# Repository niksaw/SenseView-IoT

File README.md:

# SenseView – Modular IoT Environmental Monitoring Platform

> **An end-to-end IoT platform engineered from concept to deployment, integrating custom hardware, embedded firmware, and a scalable edge-to-cloud data pipeline.**

## Overview

SenseView is a battery-powered IoT environmental monitoring platform developed to demonstrate the complete lifecycle of an embedded IoT system—from hardware design and firmware development to data acquisition, visualization, and cloud integration.

Originally developed as part of a Master's thesis in Electrical and Microsystems Engineering, the project was driven by research objectives emphasizing measurement quality, reliability, modularity, and low-power operation rather than minimizing hardware cost. Consequently, hardware and sensor selection were based on engineering requirements rather than cost optimization.

The platform combines a custom-designed ESP32-C6 sensor node, modular embedded firmware, and a complete MQTT-based backend capable of simultaneously storing data in both local and cloud time-series databases. Although the current implementation uses Zigbee communication, the architecture was intentionally designed to support future migration to Wi-Fi or Thread/Matter with minimal changes.

---

# System Architecture

---

# Engineering Highlights

- Designed and manufactured a custom ESP32-C6 PCB using KiCad.
- Developed embedded firmware for environmental sensing, sensor validation, preprocessing, fault detection, battery monitoring, and automated irrigation control.
- Built a complete MQTT-based IoT backend using Mosquitto, Telegraf, InfluxDB, and Grafana.
- Implemented simultaneous local and cloud data storage using Telegraf dual-output configuration.
- Designed the communication layer to remain extensible to Zigbee, Wi-Fi, and Thread/Matter.
- Designed a custom deployment enclosure using SolidWorks.
- Integrated environmental sensing, data visualization, and irrigation control into a single modular IoT platform.

---

# Technology Stack

| Category | Technology |
|-----------|------------|
| Microcontroller | ESP32-C6 |
| Sensors | SCD40, BME680, TSL2591, SEN0193 |
| Communication | Zigbee (Extensible to Wi-Fi & Thread/Matter) |
| Firmware | Arduino Framework (C++) |
| MQTT Broker | Mosquitto |
| Data Collection | Telegraf |
| Database | InfluxDB + InfluxDB Cloud |
| Dashboard | Grafana + Grafana Cloud |
| PCB Design | KiCad |
| Mechanical Design | SolidWorks |

---

# Gallery

## Complete Device
Battery-powered prototype assembled inside the custom enclosure prior to deployment.

## Custom PCB
PCB integrating the ESP32-C6, environmental sensors, battery management, and expansion headers.

## Grafana Dashboard
Real-time visualization of environmental data collected from the deployed sensor node

## Deployment
Prototype deployed for indoor environmental monitoring

---

# Hardware

## Microcontroller

- ESP32-C6 Development Board

## Sensors

| Sensor | Purpose |
|---------|----------|
| Sensirion SCD40 | CO₂ Concentration |
| Bosch BME680 | Temperature, Humidity, Pressure, VOC |
| Adafruit TSL2591 | Ambient Light |
| DFRobot SEN0193 | Soil Moisture |

## Additional Hardware

- Custom PCB
- Li-Po Battery
- Solenoid Valve
- Custom 3D Printed Enclosure

---

# Software Architecture

## Embedded Firmware

- Sensor acquisition
- Sensor validation
- Data preprocessing
- Battery monitoring
- Irrigation control
- Fault detection

## Communication

- Zigbee
- Zigbee2MQTT

## Backend

- Mosquitto MQTT Broker
- Telegraf
- Local InfluxDB
- InfluxDB Cloud
- Local Grafana
- Grafana Cloud

---

# Repository Structure

```text
firmware/
    ESP32-C6 firmware

hardware/
    bom/
    gerbers/
    kicad/

enclosure/
    SolidWorks enclosure

images/
    architecture/
    dashboard/
    hardware/
    showcase/
```

---
# Engineering Decisions

| Decision | Reason |
|----------|--------|
| ESP32-C6 | Supports Zigbee, Wi-Fi and native Thread, enabling a modular communication architecture. |
| Zigbee | Low-power communication suitable for battery-operated IoT devices and readily available laboratory infrastructure. |
| BME680 | Higher measurement capability including VOC sensing compared to BME280. |
| Custom PCB | Improved robustness, compactness and deployment reliability compared to breadboard prototypes. |
| Telegraf | Flexible preprocessing and simultaneous transmission to both local and cloud InfluxDB instances. |

---

# Engineering Challenges

Some of the most significant engineering challenges encountered during this project included:

- Designing a reliable battery-powered power supply and custom PCB.
- Developing a complete IoT backend from MQTT through cloud visualization.
- Developing custom Zigbee2MQTT integration for seamless communication with the local IoT infrastructure.
- Designing a modular architecture capable of supporting future communication technologies with minimal hardware changes.

---

# Future Improvements

- Wi-Fi communication backend
- Native Thread / Matter implementation
- OTA firmware updates
- Further power optimization
- Configuration interface
- Mobile application

---

# Project Background

This project was developed as part of a Master's thesis in Electrical and Microsystems Engineering at OTH Regensburg.

Rather than focusing on building a single-purpose plant monitoring device, the objective was to engineer a reusable IoT platform capable of supporting environmental sensing applications while remaining modular, scalable and suitable for future communication technologies.

---

# Acknowledgements

I would like to thank my thesis supervisor and OTH Regensburg for providing the opportunity and research environment for this project.

---

# License

This project is licensed under the MIT License.

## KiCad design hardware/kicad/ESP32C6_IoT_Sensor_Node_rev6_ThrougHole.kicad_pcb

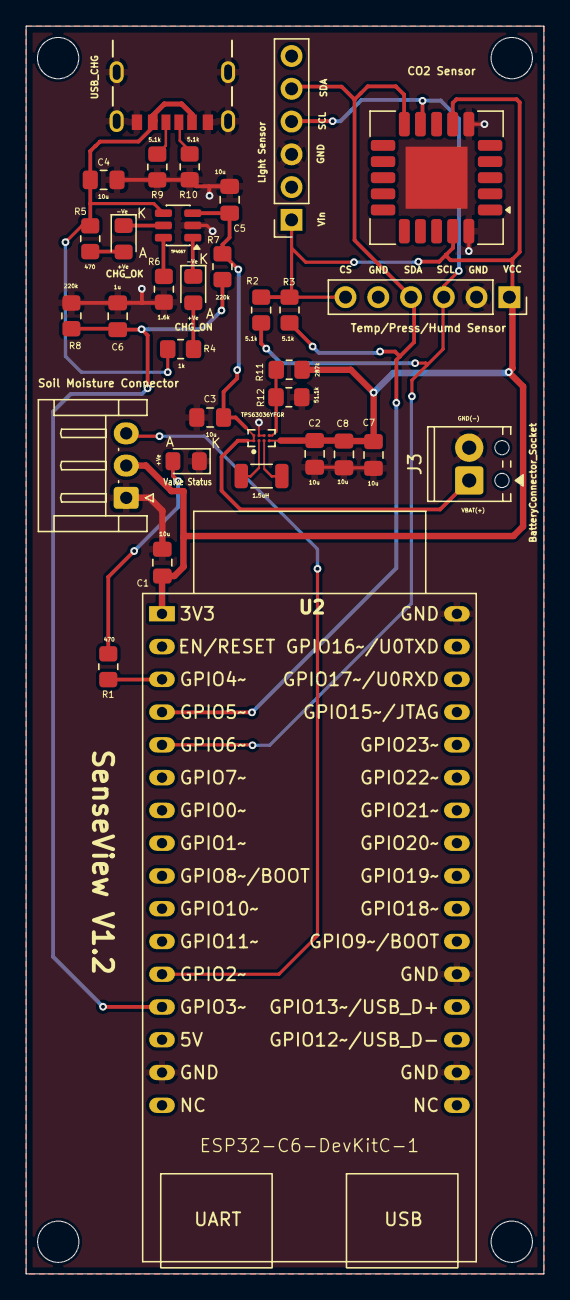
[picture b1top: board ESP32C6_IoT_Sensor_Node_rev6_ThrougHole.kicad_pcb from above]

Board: 2 copper layers, 40.1 x 96.7 mm, 33 parts (0 on the bottom side), 20 nets.

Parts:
C1, C2, C3, C4, C5, C7, C8: 10u; C_0805_2012Metric_Pad1.18x1.45mm_HandSolder
C6: 1u; C_0805_2012Metric_Pad1.18x1.45mm_HandSolder
D1: CHG_OK; LED_0805_2012Metric_Pad1.15x1.40mm_HandSolder
D2: Valve Status; LED_0805_2012Metric_Pad1.15x1.40mm_HandSolder
D3: CHG_ON; LED_0805_2012Metric_Pad1.15x1.40mm_HandSolder
J1: Soil Moisture Connector; JST_EH_S3B-EH_1x03_P2.50mm_Horizontal
J2: USB_CHG; MOLEX_2171750001
J3: BatteryConnector_Socket; TerminalBlock_Phoenix_MPT-0,5-2-2.54_1x02_P2.54mm_Horizontal
L1: 1.5uH; L_1206_3216Metric
R1, R5: 470; R_0805_2012Metric_Pad1.20x1.40mm_HandSolder
R2, R3, R9, R10: 5.1k; R_0805_2012Metric_Pad1.20x1.40mm_HandSolder
R4: 1k; R_0805_2012Metric_Pad1.20x1.40mm_HandSolder
R6: 1.6k; R_0805_2012Metric_Pad1.20x1.40mm_HandSolder
R7, R8: 220k; R_0805_2012Metric_Pad1.20x1.40mm_HandSolder
R11: 287k; R_0805_2012Metric_Pad1.20x1.40mm_HandSolder
R12: 51.1k; R_0805_2012Metric_Pad1.20x1.40mm_HandSolder
U1: Temp/Press/Humd Sensor; PinSocket_1x06_P2.54mm_Vertical
U2: ESP32-C6-DevKitC-1
U3: CO2 Sensor; Sensirion_SCD4x-1EP_10.1x10.1mm_P1.25mm_EP4.8x4.8mm
U4: Light Sensor; PinSocket_1x06_P2.54mm_Vertical
U5: TP4057; TSOT-23-6
U6: TPS63036YFGR; BGA8N40P4X2_181X107X62N

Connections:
5V: C4.1, J2.A9 (VBUS1), J2.B9 (VBUS2), R4.1, R5.1, U5.4 (V_{CC})
+3.3V: C1.1, C2.1, C7.1, C8.1, J1.2, R2.2, R3.2, R11.2, U1.1 (VCC), U1.6 (CS), U2.1 (3V3), U3.7 (VDD), U3.19 (VDD), U4.1 (VIN), U6.D1 (VOUT)
ADC: C6.1, R7.2, R8.1, U2.13 (GPIO3)
GND: C1.2, C2.2, C3.2, C4.2, C5.2, C6.2, C7.2, C8.2, D2.1 (K), J1.1, J2.A12 (GND1), J2.B12 (GND2), J2.SH1 (SHIELD1), J2.SH2 (SHIELD2), J2.SH3 (SHIELD3), J2.SH4 (SHIELD4), J3.2, R6.1, R8.2, R9.1, R10.1, R12.1, U1.2 (GND), U2.15 (GND), U2.18 (GND), U2.21 (GND), U2.32 (GND), U3.6 (GND), U3.20 (GND), U3.21 (GND), U4.3 (GND), U5.2 (GND), U6.B2 (PS/SYNC), U6.C2 (GND)
I2C_SCL: R2.1, U1.3 (SCL), U2.5 (GPIO6), U3.9 (SCL), U4.4 (SCL)
I2C_SDA: R3.1, U1.4 (SDA), U2.4 (GPIO5/MTDI), U3.10 (SDA), U4.5 (SDA)
unnamed: D1.2 (A), R5.2
unnamed: D1.1 (K), U5.5 (STDBY)
unnamed: D2.2 (A), R1.1
unnamed: D3.2 (A), R4.2
unnamed: D3.1 (K), U5.1 (~CHRG)
unnamed: J2.A5 (CC1), R10.2
unnamed: J2.B5 (CC2), R9.2
unnamed: R1.2, U2.3 (GPIO4/MTMS)
unnamed: R6.2, U5.6 (PROG)
unnamed: R11.1, R12.2, U6.D2 (FB)
unnamed: L1.1, U6.B1 (L1)
unnamed: L1.2, U6.C1 (L2)
SMS: J1.3, U2.12 (GPIO2)
VBAT: C3.1, C5.1, J3.1, R7.1, U5.3 (BAT), U6.A1 (VIN), U6.A2 (EN)

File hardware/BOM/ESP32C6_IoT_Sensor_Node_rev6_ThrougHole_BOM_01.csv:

Reference,Qty,Value,DNP,Exclude from BOM,Exclude from Board,Footprint,Datasheet,JLCPCB Part #
"C1,C2,C3,C4,C5,C7,C8",7,10u,,,,Capacitor_SMD:C_0805_2012Metric_Pad1.18x1.45mm_HandSolder,~,C440198
C6,1,1u,,,,Capacitor_SMD:C_0805_2012Metric_Pad1.18x1.45mm_HandSolder,~,C28323
D1,1,Green LED,,,,LED_SMD:LED_0805_2012Metric_Pad1.15x1.40mm_HandSolder,~,C2297
D2,1,Valve LED Indicator,,,,LED_SMD:LED_0805_2012Metric_Pad1.15x1.40mm_HandSolder,~,C434433
D3,1,RED LED,,,,LED_SMD:LED_0805_2012Metric_Pad1.15x1.40mm_HandSolder,~,C284871
J1,1,SEN0193_Soil_Moisture Connector,DNP,,,Connector_JST:JST_EH_S3B-EH_1x03_P2.50mm_Horizontal,~,
J2,1,2171750001,,,,217175-0001 USB Type C:MOLEX_2171750001,,C3197922
J3,1,BatteryConnector_Socket,,,,"TerminalBlock_Phoenix:TerminalBlock_Phoenix_MPT-0,5-2-2.54_1x02_P2.54mm_Horizontal",~,C918120
L1,1,1.5uH,,,,Inductor_SMD:L_1206_3216Metric,~,C2885920
"R1,R5",2,470,,,,Resistor_SMD:R_0805_2012Metric_Pad1.20x1.40mm_HandSolder,~,C17710
"R2,R3,R9,R10",4,5.1k,,,,Resistor_SMD:R_0805_2012Metric_Pad1.20x1.40mm_HandSolder,~,C27834
R4,1,1k,,,,Resistor_SMD:R_0805_2012Metric_Pad1.20x1.40mm_HandSolder,~,C17513
R6,1,1.6k,,,,Resistor_SMD:R_0805_2012Metric_Pad1.20x1.40mm_HandSolder,~,C2933328
"R7,R8",2,220k,,,,Resistor_SMD:R_0805_2012Metric_Pad1.20x1.40mm_HandSolder,~,C17556
R11,1,287k,,,,Resistor_SMD:R_0805_2012Metric_Pad1.20x1.40mm_HandSolder,~,C2933396
R12,1,51.1k,,,,Resistor_SMD:R_0805_2012Metric_Pad1.20x1.40mm_HandSolder,~,C138264
U1,1,BME680_THT,DNP,,,Connector_PinSocket_2.54mm:PinSocket_1x06_P2.54mm_Vertical,https://www.joy-it.net/files/files/Produkte/SEN-BME680/SEN-B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,
U2,1,ESP32-C6-DevKitC-1,DNP,,,Espressif:ESP32-C6-DevKitC-1,https://docs.espressif.com/projects/espressif-esp-dev-kits/e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,
U3,1,SCD40-D-R2,,,,Sensor:Sensirion_SCD4x-1EP_10.1x10.1mm_P1.25mm_EP4.8x4.8mm,https://sensirion.com/media/documents/E0F04247/631EF271/CD_D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,C3659421
U4,1,TSL 2591_THT,DNP,,,Connector_PinSocket_2.54mm:PinSocket_1x06_P2.54mm_Vertical,https://ams.com/documents/20143/9331680/TSL2591_DS000338_7-00.pdf,
U5,1,TP4057,,,,Package_TO_SOT_SMD:TSOT-23-6,http://toppwr.com/uploadfile/file/20230304/640302a47b738.pdf,C725791
U6,1,TPS63036YFGR,,,,TPS63036YFGR:BGA8N40P4X2_181X107X62N,,C283955

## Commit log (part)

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2026-06-28 Initial project structure and source files
2026-06-28 Add comprehensive project README
2026-06-28 Add system architecture diagram
2026-06-28 Improve project README

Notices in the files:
README.md:
License: MIT
